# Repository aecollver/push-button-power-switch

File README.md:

# Push-Button Power Switch

A discrete, high-side MOSFET power switch controlled by a single momentary pushbutton. Designed for battery-powered electronics without requiring a microcontroller or dedicated power-management IC.

## Overview

This circuit was developed as part of a small robotics project where I wanted to replace a mechanical power switch with a momentary pushbutton.

The goal was a simple circuit that could toggle power with a short button press, consume minimal power when switched off, and change state at most once per press, regardless of how long the button was held.

Although this sounds straightforward, I found that many existing discrete power-latch designs were surprisingly finicky. Some were clever and used very few components, but were difficult to understand or sensitive to timing. Others behaved unexpectedly when subjected to rapid button presses or when the button was held down too long, sometimes toggling the power state unintentionally. I wanted a circuit that behaved predictably, even when the button wasn't operated exactly as intended.

This repository contains the KiCad hardware design and bill of materials, along with a simulation project in `simulation/` for testing the circuit directly in KiCad's simulator.

## Features

- Single momentary pushbutton for ON/OFF control
- Short press toggles power state
- Debounced input to prevent unintended toggling
- Predictable behavior during rapid presses and extended button holds
- No microcontroller or firmware required
- Dual-channel power MOSFET provides load switching and reverse-polarity protection

## How It Works

The circuit consists of several functional stages:

1. **Startup State:** Keeps the circuit switched off when power is first applied.
2. **Switch Debounce:**  Filters mechanical switch bounce to prevent unintended toggling.
3. **Button Press Detection:** Generates a pulse on the rising edge of a button press.
4. **Power-On Pulse:** Provides the initial pulse needed to activate the MOSFET latch before the ON-state feedback takes over.
5. **ON-State Feedback:** Maintains the latch after the button is released.
6. **OFF Enable Delay:** Prevents the initial button press from immediately switching the circuit off. This delay must be comfortably longer than the Power-On Pulse.
7. **Qualified OFF Trigger:** Releases the latch on a subsequent button press, once the OFF Enable Delay has elapsed.
8. **Load Switch:** Controls power delivery using a separate MOSFET, preventing capacitive loads from interfering with the latch. The hardware design uses a dual-channel power MOSFET, with one channel for load switching and the other for reverse-polarity protection.

See the schematic for component values and connections.

## Design Files

The project was created using KiCad 10.0.6.

A [preview of the PCB layout](docs/images/pcb.png) is available as a KiCad screenshot. The PCB hasn't been fabricated or tested yet.

| File | Description |
|---|---|
| **[hardware/](hardware/)** | **Hardware design** |
| [push-button-power-switch.kicad_sch](hardware/push-button-power-switch.kicad_sch) | KiCad schematic |
| [push-button-power-switch.kicad_pcb](hardware/push-button-power-switch.kicad_pcb) | KiCad PCB layout (not yet fabricated or tested) |
| [push-button-power-switch.kicad_pro](hardware/push-button-power-switch.kicad_pro) | KiCad project configuration |
| [push-button-power-switch.csv](hardware/push-button-power-switch.csv) | Hardware bill of materials (BOM) |
| **[simulation/](simulation/)** | **Simulation project** |
| [push-button-power-switch-simulation.kicad_sch](simulation/push-button-power-switch-simulation.kicad_sch) | Simulation schematic with sources and a simulated load |
| [push-button-power-switch-simulation.kicad_pro](simulation/push-button-power-switch-simulation.kicad_pro) | Simulation project configuration |
| [push-button-power-switch-simulation.wbk](simulation/push-button-power-switch-simulation.wbk) | KiCad simulation workbook with saved analysis and plot settings |

Open the project in `simulation/` to test the switching behavior using the included simulation sources and simulated load.

## Simulation and Testing

The circuit was developed through simulation and breadboard experimentation. Simulations were used to explore switching behavior across different supply voltages and load conditions, while breadboard testing confirmed basic operation.

Simulation scenarios include:

- Short button presses
- Repeated button presses
- Startup and shutdown behavior
- Different supply voltages
- Resistive and capacitive loads

The circuit was also assembled on a breadboard to verify its operation with a physical momentary pushbutton.

*Breadboard prototype of the push-button power switch.*

## Limitations

The 5–25 V input range has not been fully validated in physical hardware. Select components appropriate for your intended operating voltage and load current, paying particular attention to MOSFET gate-source voltage limits, power dissipation, and capacitor voltage ratings.

## License

Hardware design files are licensed under the CERN Open Hardware Licence Version 2 – Permissive (CERN-OHL-P-2.0). See [LICENSE](LICENSE).

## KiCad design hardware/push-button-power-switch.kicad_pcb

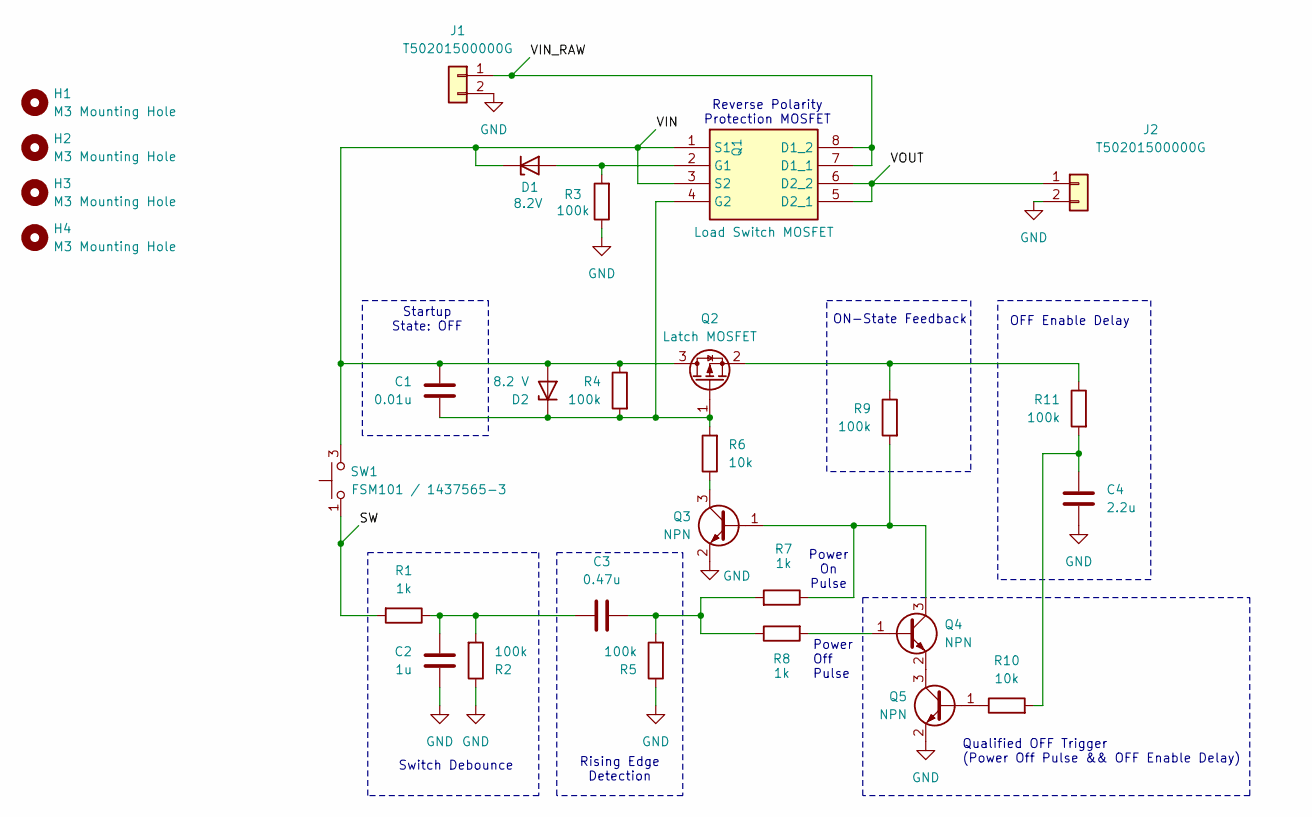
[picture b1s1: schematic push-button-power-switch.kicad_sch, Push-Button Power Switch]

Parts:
C1: 0.01u; C_0805_2012Metric_Pad1.18x1.45mm_HandSolder; Manufacturer Part Number CC0805KRX7R0BB103
C2: 1u; C_0805_2012Metric_Pad1.18x1.45mm_HandSolder; Manufacturer Part Number CC0805KFX7R8BB105
C3: 0.47u; C_0805_2012Metric_Pad1.18x1.45mm_HandSolder; Manufacturer Part Number CC0805KKX7R9BB474
C4: 2.2u; C_0805_2012Metric_Pad1.18x1.45mm_HandSolder; Manufacturer Part Number CC0805KKX7R8BB225
D1: 8.2V; D_SOD-323_HandSoldering; Manufacturer Part Number BZT52-B8V2S_R1_00001
D2: 8.2 V; D_SOD-323_HandSoldering; Manufacturer Part Number BZT52-B8V2S_R1_00001
H1, H2, H3, H4: M3 Mounting Hole; MountingHole_3.2mm_M3
J1, J2: T50201500000G; Mouser Part Number 649-T502015000J0G
Q1: Load Switch MOSFET; SOIC127P600X170-8N; Manufacturer Part Number DMP3028LSD-13; Mouser Part Number 621-DMP3028LSD-13
Q2: Latch MOSFET; SOT-23_Handsoldering; Manufacturer Part Number MMFTP3401-AQ
Q3, Q4, Q5: NPN; SOT-23_Handsoldering; Manufacturer Part Number MMBT3904
R1, R7, R8: 1k; R_0805_2012Metric_Pad1.20x1.40mm_HandSolder; Manufacturer Part Number RC0805FR-071KL
R2, R3, R4, R5, R9, R11: 100k; R_0805_2012Metric_Pad1.20x1.40mm_HandSolder; Manufacturer Part Number RC0805FR-07100KL
R6, R10: 10k; R_0805_2012Metric_Pad1.20x1.40mm_HandSolder; Manufacturer Part Number RC0805FR-0710KL
SW1: FSM101 / 1437565-3; FSM101

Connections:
/SW: R1.2, SW1.1, SW1.2
/VIN: C1.1, D1.1 (K), D2.2 (A), Q1.1 (S1), Q1.3 (S2), Q2.3 (D), R4.1, SW1.3, SW1.4
/VIN_RAW: J1.1, Q1.7 (D1_1), Q1.8 (D1_2)
/VOUT: J2.1, Q1.5 (D2_1), Q1.6 (D2_2)
GND: C2.2, C4.2, J1.2, J2.2, Q3.2 (E), Q5.2 (E), R2.1, R3.1, R5.1
unnamed: C2.1, C3.1, R1.1, R2.2
unnamed: C3.2, R5.2, R7.2, R8.1
unnamed: C4.1, R10.2, R11.2
unnamed: D1.2 (A), Q1.2 (G1), R3.2
unnamed: C1.2, D2.1 (K), Q1.4 (G2), Q2.1 (G), R4.2, R6.2
unnamed: Q2.2 (S), R9.1, R11.1
unnamed: Q3.1 (B), Q4.3 (C), R7.1, R9.2
unnamed: Q3.3 (C), R6.1
unnamed: Q4.1 (B), R8.2
unnamed: Q4.2 (E), Q5.3 (C)
unnamed: Q5.1 (B), R10.1

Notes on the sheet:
OFF Enable Delay
Qualified OFF Trigger (Power Off Pulse && OFF Enable Delay)
ON-State Feedback
Power Off Pulse
Reverse Polarity Protection MOSFET
Power On Pulse
Rising Edge Detection
Startup State: OFF
Switch Debounce

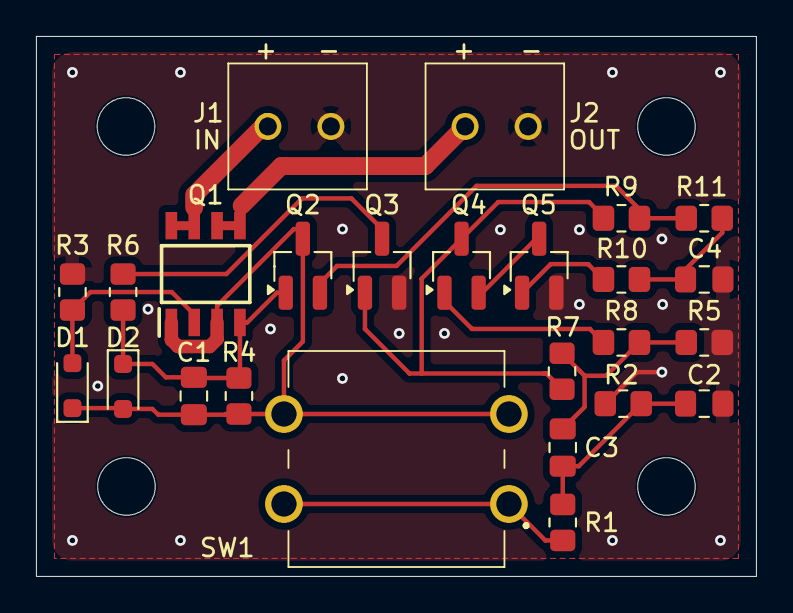
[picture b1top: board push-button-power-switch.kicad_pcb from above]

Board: 2 copper layers, 40.0 x 30.0 mm, 29 parts (0 on the bottom side), 16 nets.
